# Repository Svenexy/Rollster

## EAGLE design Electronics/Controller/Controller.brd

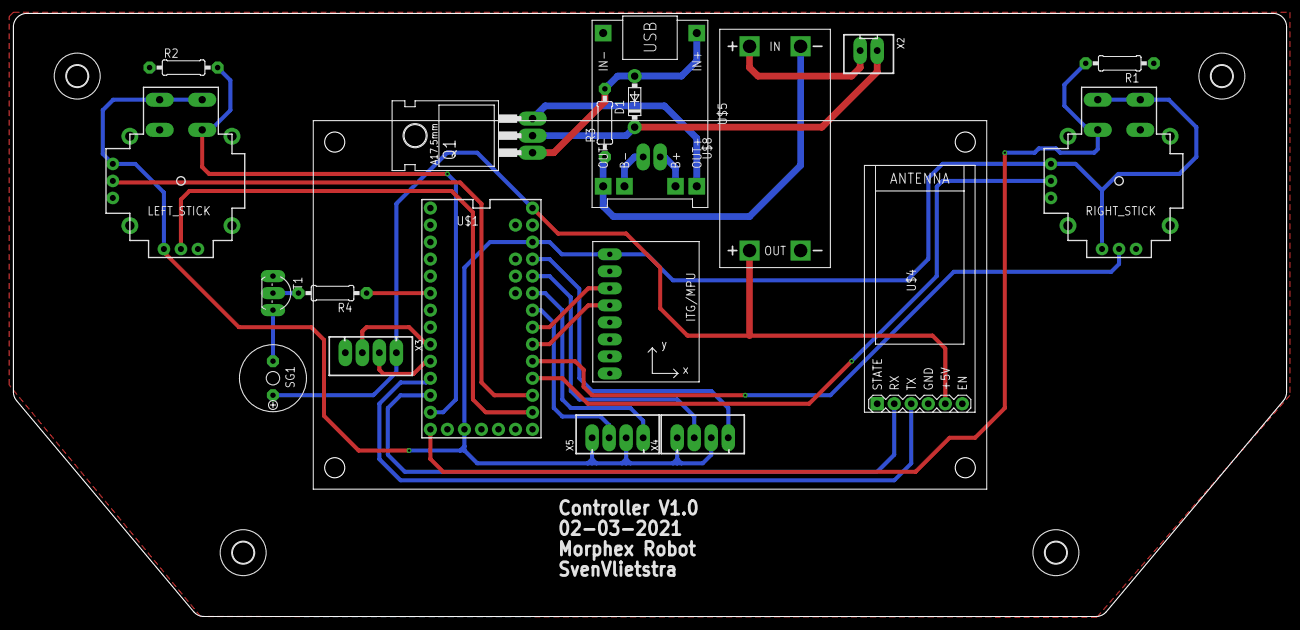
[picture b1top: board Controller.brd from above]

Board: 2 copper layers, 190.0 x 90.0 mm, 25 parts (1 on the bottom side), 29 nets.

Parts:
D1: 1N5819-B; DO41-7.6
LEFT_STICK: JOYSTICKPTH; JOYSTICK
Q1: NDP6020P; TO220BH
R1, R2: 10k; 0207/10
R3: 10K; 0207/10
R4: 2K2; 0207/10
RIGHT_STICK: JOYSTICKPTH; JOYSTICK
SG1: Buzzer; 5MM
T1: TO92-EBC
U1: GY-521MPU6050; GY-521
U$1: TEENSY_LC_ALL_PINS; TEENSY_3.0-3.2&LC_ALL_PINS
U$2, U$3, U$6, U$7: 3,2
U$4: WIRELESS-BLUETOOTH-HC-05
U$5: BATTERY-CHARGER-LI-PROT
U$8: DC-DC-STEP-UP-MT3608
U$9: NX4832K035
X1: Battery; JST-XH-02-PACKAGE-LONG-PAD
X2: Switch; JST-XH-02-PACKAGE-LONG-PAD
X3: Nextion; JST-XH-04-PACKAGE-LONG-PAD
X4: BUT_L; JST-XH-04-PACKAGE-LONG-PAD
X5: BUT_R; JST-XH-04-PACKAGE-LONG-PAD

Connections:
+3V3: LEFT_STICK.B1A, LEFT_STICK.B1B, LEFT_STICK.H1, LEFT_STICK.V1, RIGHT_STICK.B1A, RIGHT_STICK.B1B, RIGHT_STICK.H1, RIGHT_STICK.V1, U1.VCC, U$1.3.3V, U$1.3.3V1, X4.1, X4.3, X5.1, X5.3
+5V: SG1.P$2, U$1.VIN, U$4.5, U$8.OUT+, X3.1
BL_RX: U$1.10, U$4.2
BL_TX: U$1.9, U$4.3
BUT_1: U$1.22/A8, X4.2
BUT_2: U$1.23/A9, X4.4
BUT_3: U$1.20/A6, X5.2
BUT_4: U$1.21/A7, X5.4
BUZZER: R4.1, U$1.4
GND: LEFT_STICK.H3, LEFT_STICK.MOUNT1, LEFT_STICK.MOUNT2, LEFT_STICK.MOUNT3, LEFT_STICK.MOUNT4, LEFT_STICK.V3, R1.1, R2.1, RIGHT_STICK.H3, RIGHT_STICK.MOUNT1, RIGHT_STICK.MOUNT2, RIGHT_STICK.MOUNT3, RIGHT_STICK.MOUNT4, RIGHT_STICK.V3, T1.E, U1.GND, U$1.AGND, U$1.GND, U$1.GND1, U$4.4, U$8.OUT-, X3.4
GY_SCL: U1.SCL, U$1.19/A5
GY_SDA: U1.SDA, U$1.18/A4
unnamed: R3.1, U$5.OUT-, U$8.IN-
unnamed: U$5.B+, X1.1
unnamed: U$5.B-, X1.2
unnamed: D1.C, Q1.D, X2.1
unnamed: Q1.S, U$5.OUT+
unnamed: U$8.IN+, X2.2
unnamed: R4.2, T1.B
unnamed: SG1.P$1, T1.C
unnamed: D1.A, Q1.G, R3.2, U$5.IN+
NEX_RX: U$1.8, X3.2
NEX_TX: U$1.7, X3.3
SW1: LEFT_STICK.B2A, LEFT_STICK.B2B, R2.2, U$1.11
SW2: R1.2, RIGHT_STICK.B2A, RIGHT_STICK.B2B, U$1.12
X-AXIS1: LEFT_STICK.V2, U$1.15/A1
X-AXIS2: RIGHT_STICK.V2, U$1.16/A2
Y-AXIS1: LEFT_STICK.H2, U$1.14/A0
Y-AXIS2: RIGHT_STICK.H2, U$1.17/A3

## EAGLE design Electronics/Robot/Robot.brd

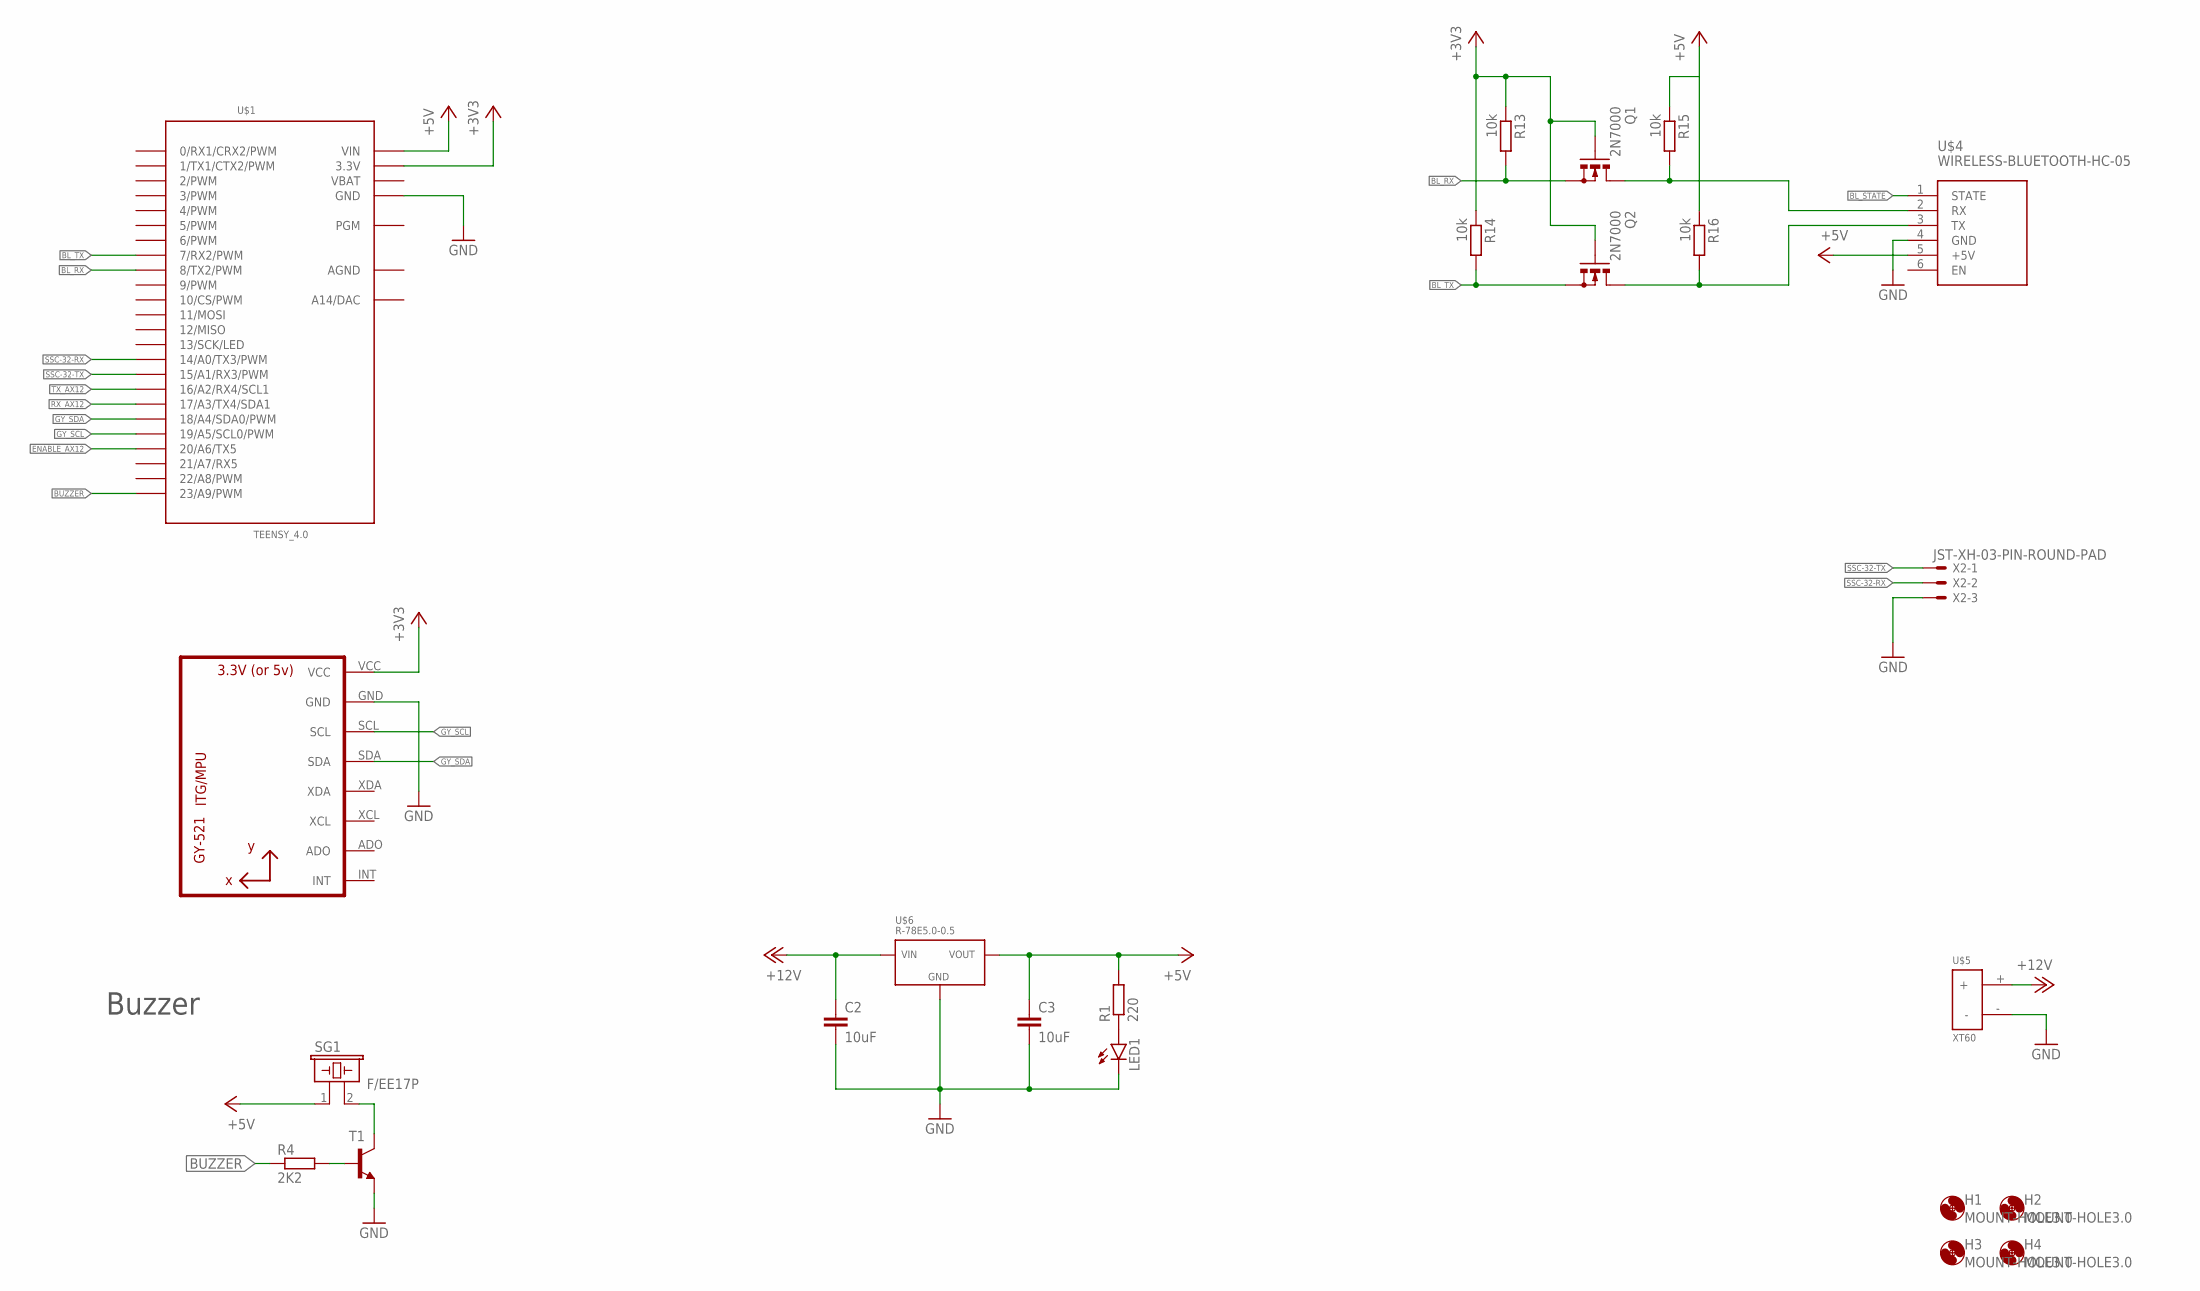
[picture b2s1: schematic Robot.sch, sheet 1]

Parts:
C2, C3: 10uF; C050-024X044
H1, H2, H3, H4: MOUNT-HOLE3.0; 3,0
LED1: LED5MM
Q1, Q2: 2N7000; SOT54E
R1: 220; 0207/10
R4: 2K2; 0207/10
R13, R14, R15, R16: 10k; 0207/10
SG1: F/EE17P
T1: -NPN-TO92-EBC; TO92-EBC
U1: GY-521MPU6050; GY-521
U$1: TEENSY_4.0
U$4: WIRELESS-BLUETOOTH-HC-05
U$5: XT60
U$6: R-78E5.0-0.5
X2: JST-XH-03-PIN-ROUND-PAD; JST-XH-03-PACKAGE-ROUND-PAD

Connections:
+3V3: U1.VCC, U$1.3V3 (3.3V), U$1.3V3_1 (3.3V)
+5V: C3.1, R1.2, SG1.1, U$1.VIN, U$4.5 (+5V), U$6.VOUT; also elsewhere on the board
+12V: C2.1, U$5.+, U$6.VIN; also elsewhere on the board
AGND: U$1.AGND
BL_RX: Q1.S, R13.2, U$1.8 (8/TX2/PWM)
BL_STATE: U$4.1 (STATE)
BL_TX: Q2.S, R14.2, U$1.7 (7/RX2/PWM)
BUZZER: R4.1, U$1.23 (23/A9/PWM)
ENABLE_AX12: U$1.20 (20/A6/TX5); also elsewhere on the board
GND: C2.2, C3.2, LED1.K (C), T1.E, U1.GND, U$1.GND, U$1.GND2 (GND), U$4.4 (GND), U$5.-, U$6.GND, X2.3; also elsewhere on the board
GY_SCL: U1.SCL, U$1.19 (19/A5/SCL0/PWM)
GY_SDA: U1.SDA, U$1.18 (18/A4/SDA0/PWM)
unnamed: Q1.G, Q2.G, R13.1, R14.1
unnamed: R15.1, R16.1
unnamed: LED1.A, R1.1
unnamed: R4.2, T1.B
unnamed: SG1.2, T1.C
unnamed: Q1.D, R15.2, U$4.2 (RX)
unnamed: Q2.D, R16.2, U$4.3 (TX)
RX_AX12: U$1.17 (17/A3/TX4/SDA1); also elsewhere on the board
SSC-32-RX: U$1.14 (14/A0/TX3/PWM), X2.2
SSC-32-TX: U$1.15 (15/A1/RX3/PWM), X2.1
TX_AX12: U$1.16 (16/A2/RX4/SCL1); also elsewhere on the board
VBAT: U$1.VBAT

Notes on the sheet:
Buzzer

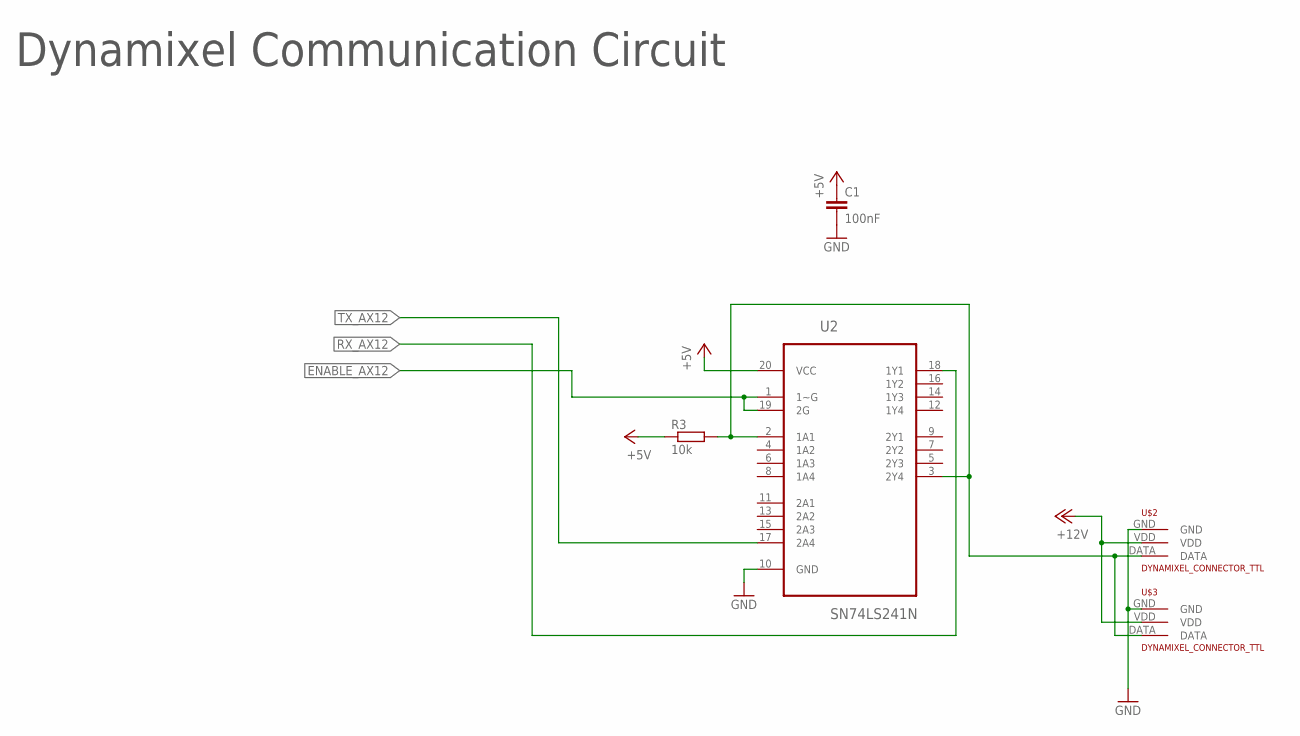
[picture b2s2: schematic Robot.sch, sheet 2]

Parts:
C1: 100nF; C050-024X044
R3: 10k; 0207/10
U2: SN74LS241N; DIP254P762X508-20
U$2, U$3: DYNAMIXEL_CONNECTOR_TTL

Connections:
+5V: C1.1, R3.1, U2.20 (VCC); also elsewhere on the board
+12V: U$2.VDD, U$3.VDD; also elsewhere on the board
DATA: R3.2, U2.2 (1A1), U2.3 (2Y4), U$2.DATA, U$3.DATA
ENABLE_AX12: U2.1 (1~G), U2.19 (2G); also elsewhere on the board
GND: C1.2, U2.10 (GND), U$2.GND, U$3.GND; also elsewhere on the board
RX_AX12: U2.18 (1Y1); also elsewhere on the board
TX_AX12: U2.17 (2A4); also elsewhere on the board

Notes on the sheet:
Dynamixel Communication Circuit

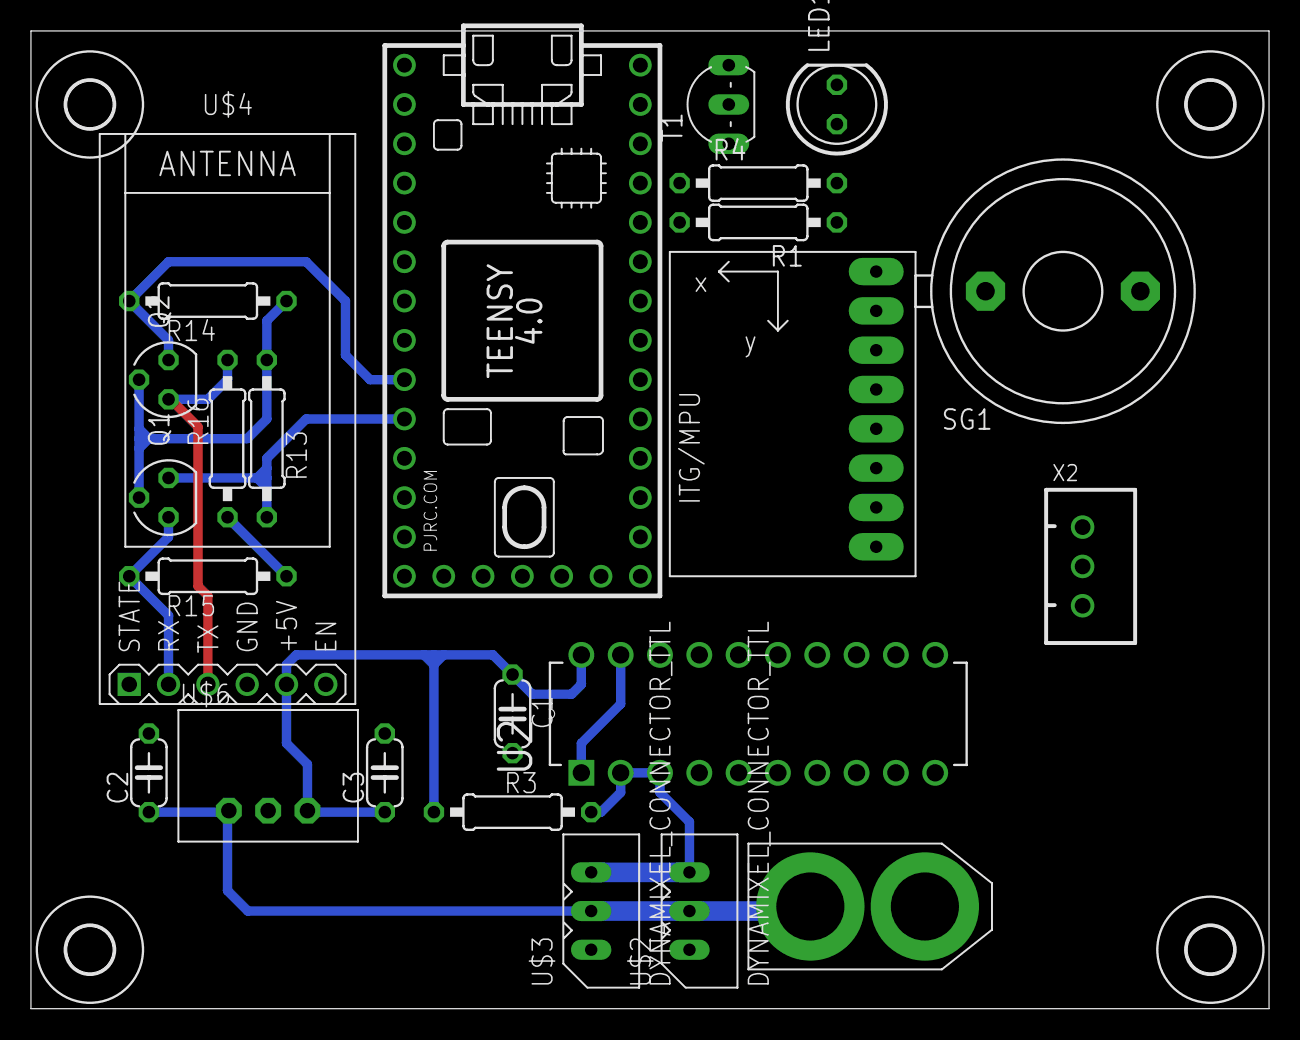
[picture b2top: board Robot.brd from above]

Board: 2 copper layers, 80.0 x 63.2 mm, 28 parts (0 on the bottom side), 22 nets.

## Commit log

2020-08-01 Create a nice fit PCB
    Creating a nice fit for the PCB in the controller so i have the most working area.
2020-08-01 Schematics made
2020-08-01 Battery Charger added
2020-08-04 Automatic source change
    Added automatic source change and fixing librabry's for better overview
2020-08-07 cache clear
2020-08-10 Buzzer, Teensy 4.0 Robot
2020-08-11 Fixed Gears and made PCB
2020-08-26 Changed the number of tooths in the gears
2020-11-03 Completed all routes
    Completed all routes and changed the P-Channel mosfet to a NDP6020P
2020-11-03 Changed model with new PCB
2020-11-03 Added some documentation
2020-11-03 Name change
2020-11-09 Added Nextion in Board Layout
    Added nextion in board layout and made the height 10mm for a standoff. Changed de JST connectors from 2mm to 2,54 spacing
2020-11-10 Frame change
2020-11-10 5V added & better layout
2020-11-15 Last changes
2021-03-15 Changed Buzzer
2021-06-29 Starting version 2 with AX-12A Servo's

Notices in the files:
parts and their libraries:
TP4056: Released under the Creative Commons Attribution 4.0 International License: http://creativecommons.org/licenses/by/4.0
